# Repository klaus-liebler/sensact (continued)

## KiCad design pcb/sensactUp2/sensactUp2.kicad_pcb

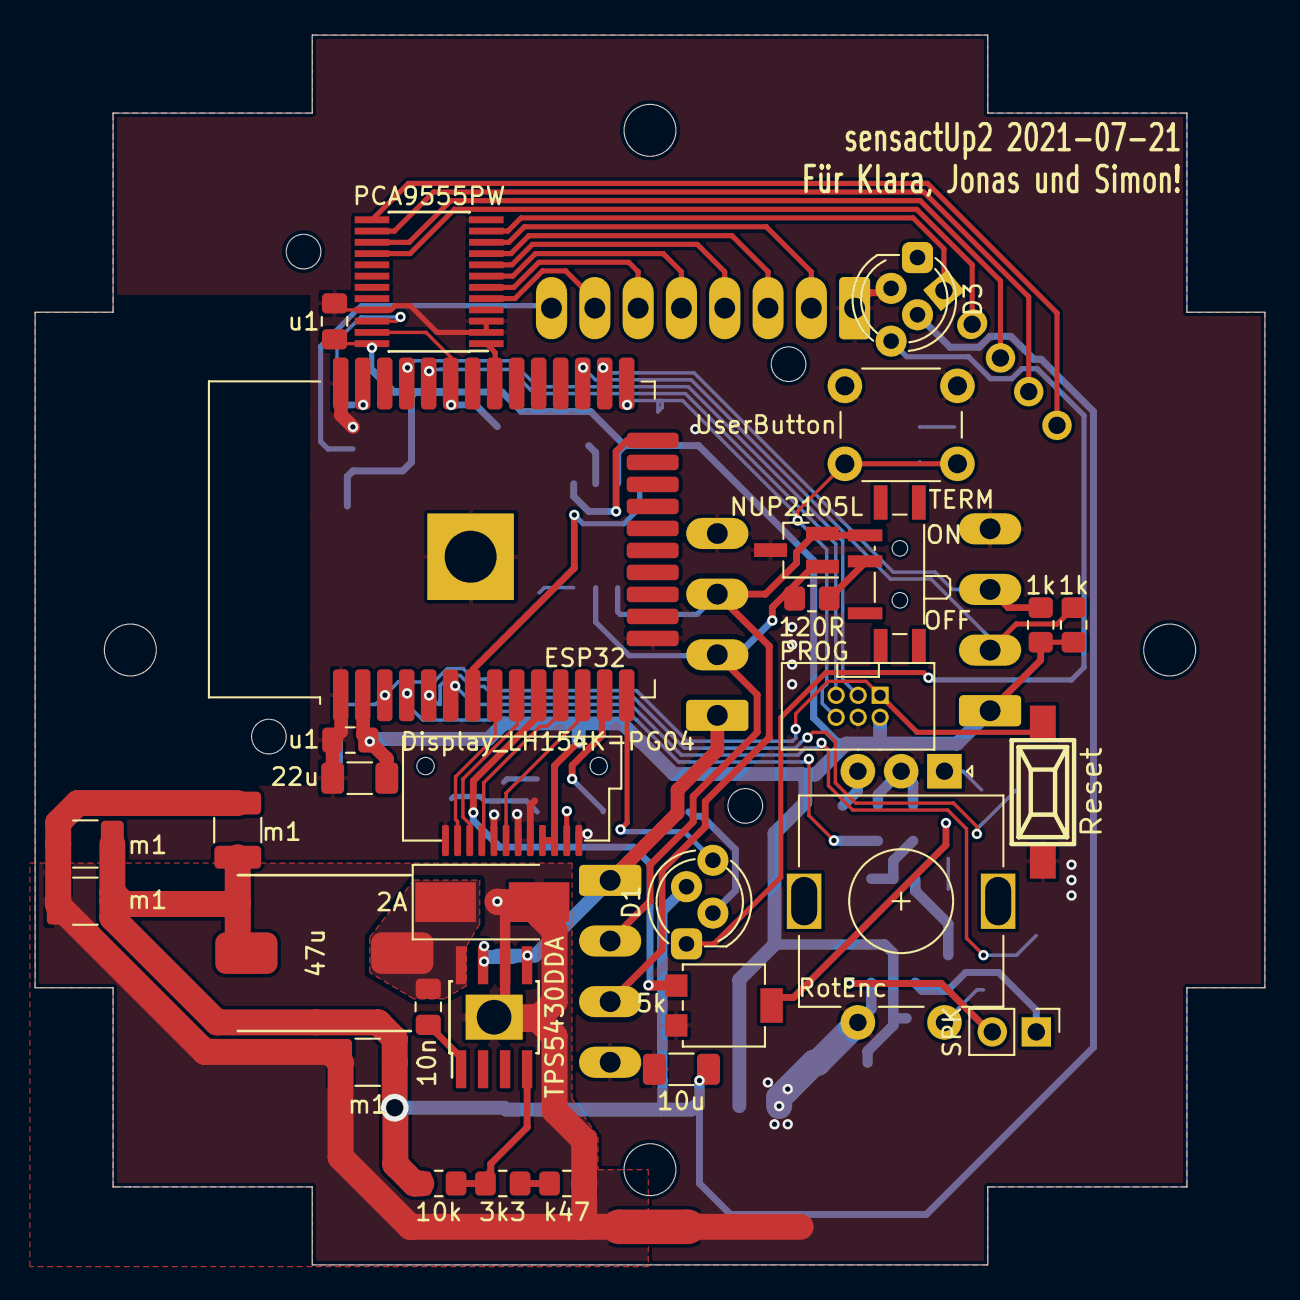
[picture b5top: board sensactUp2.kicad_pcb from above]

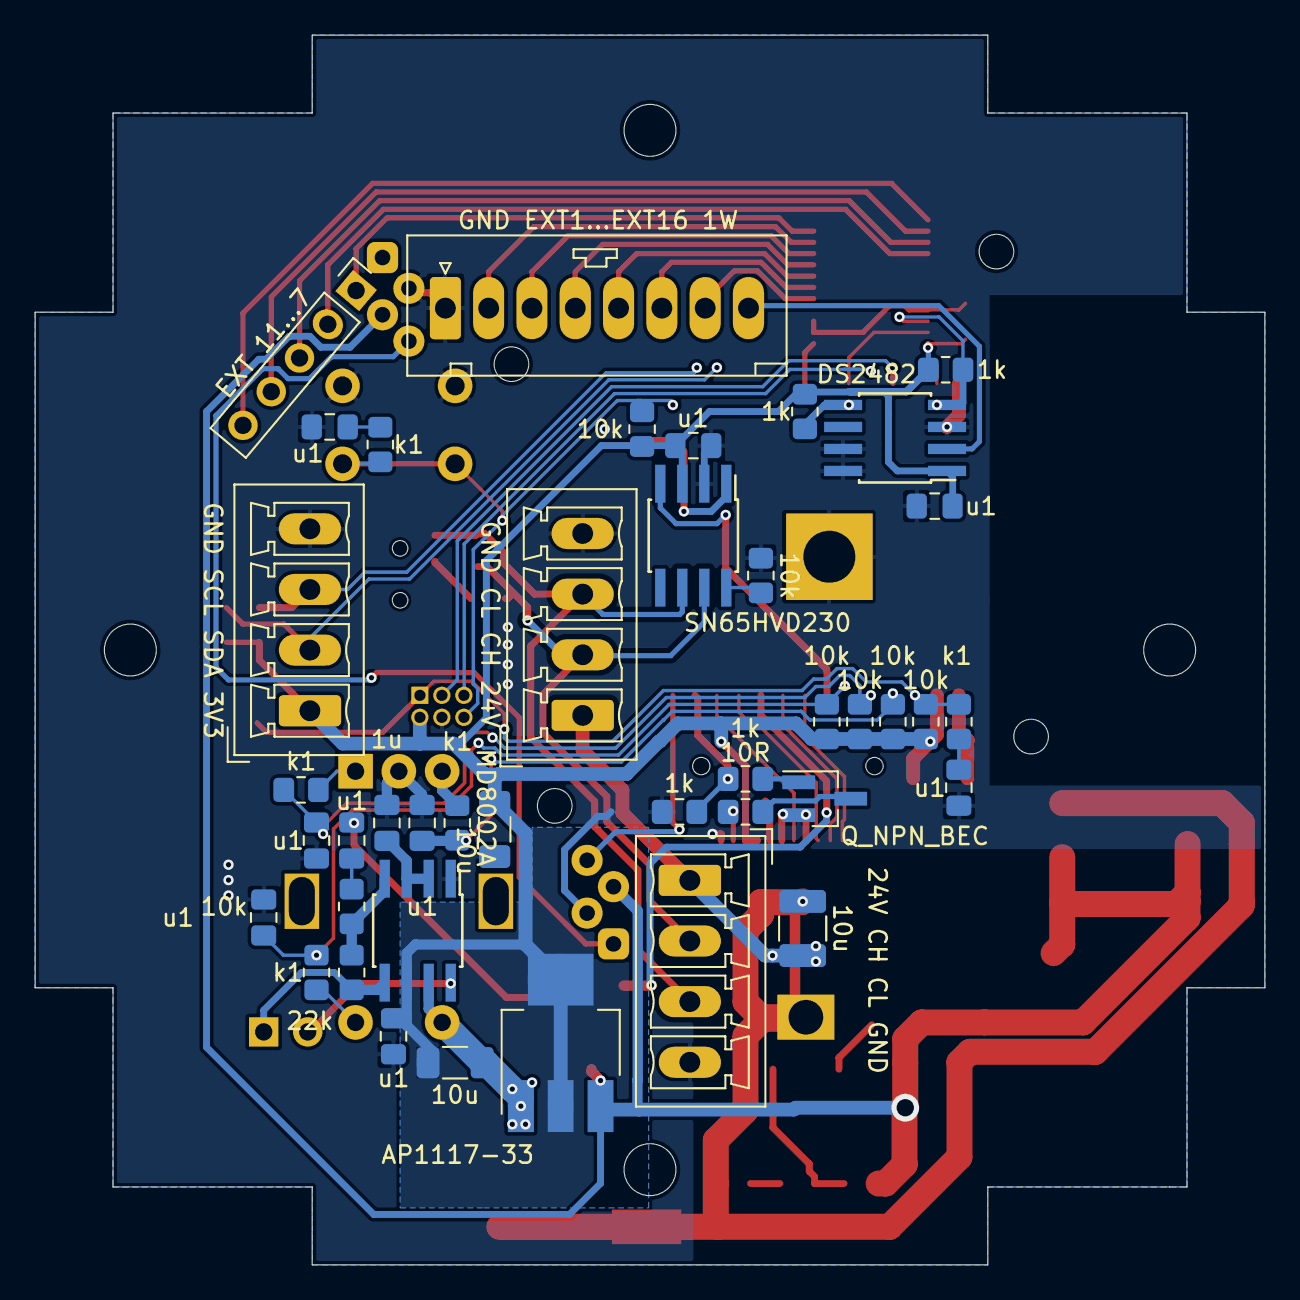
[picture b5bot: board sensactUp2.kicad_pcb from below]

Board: 2 copper layers, 71.0 x 71.0 mm, 73 parts (41 on the bottom side), 61 nets.

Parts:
C1: 22u; C_1206_3216Metric_Pad1.33x1.80mm_HandSolder
C2, C3, C4, C5, C7, C8, C9, C10, C18, C21, C22: u1; C_0805_2012Metric_Pad1.18x1.45mm_HandSolder
C6: 1u; C_0805_2012Metric_Pad1.18x1.45mm_HandSolder
C11, C19, C20: 10u; C_1206_3216Metric_Pad1.33x1.80mm_HandSolder
C12: 10u; C_1210_3225Metric_Pad1.33x2.70mm_HandSolder
C13: 10n; C_0805_2012Metric_Pad1.18x1.45mm_HandSolder
C14, C15, C16, C17: m1; C_1210_3225Metric_Pad1.33x2.70mm_HandSolder
D1: ROT_LED; LED_D5.0mm-4_RGB_Staggered_Pins
D2: 2A; D_SMB_Handsoldering
D3: USER_LED; LED_D5.0mm-4_RGB_Staggered_Pins
D4: NUP2105L; SOT-23_Handsoldering
IC1: MD8002A; SOIC-8_3.9x4.9mm_Pitch1.27mm_handsolder
J1: PROG; IDC_2x03_P1.27mm_Vertical
J2: GND CL CH 24V; PhoenixContact_MCV_1,5_4-G-3.5_1x04_P3.50mm_Vertical
J3: GND SCL SDA 3V3; PhoenixContact_MCV_1,5_4-G-3.5_1x04_P3.50mm_Vertical
J4: GND EXT1...EXT16 1W; PhoenixContact_MCV_0,5_8-G-2.5_1x08_P2.50mm_vertical
J5: 24V CH CL GND; PhoenixContact_MCV_1,5_4-G-3.5_1x04_P3.50mm_Vertical
J6: EXT 11...7; PinHeader_1x05_P2.54mm_Vertical
J7: SPK; PinHeader_1x02_P2.54mm_Vertical
L1: 47u; Inductor_CDRH104_handsolder
NT1: Net-Tie_2; NetTie-2_SMD_Pad2.0mm
Q3: Q_NPN_BEC; SOT-23_Handsoldering
R1, R2, R6, R7, R9, R10, R15, R18: 10k; R_0805_2012Metric_Pad1.20x1.40mm_HandSolder
R3, R4, R5, R14, R16: k1; R_0805_2012Metric_Pad1.20x1.40mm_HandSolder
R8: 22k; R_0805_2012Metric_Pad1.20x1.40mm_HandSolder
R11: 3k3; R_0805_2012Metric_Pad1.20x1.40mm_HandSolder
R12: k47; R_0805_2012Metric_Pad1.20x1.40mm_HandSolder
R13, R20, R21, R22, R23, R52: 1k; R_0805_2012Metric_Pad1.20x1.40mm_HandSolder
R17: 10R; R_0805_2012Metric_Pad1.20x1.40mm_HandSolder
R19: 120R; R_0805_2012Metric_Pad1.20x1.40mm_HandSolder
RV1: 5k; Potentiometer_Bourns_3314G_Vertical
SW1: RotEnc; RotaryEncoder_Alps_EC11E-Switch_Vertical_H20mm
SW2: Reset; smd_push_handsolder
SW3: UserButton; SW_PUSH_6mm_H13mm
SW4: TERM; SW_SPDT_PCM12_handsolder
U1: ESP32; ESP32-WROOM-32_HANDSOLDER
U2: TPS5430DDA; SOIC-8_3.9x4.9mm_Pitch1.27mm_pad_handsolder
U3: DS2482; SOIC-8_3.9x4.9mm_Pitch1.27mm_handsolder
U4: SN65HVD230; SOIC-8_3.9x4.9mm_Pitch1.27mm_handsolder
U5: AP1117-33; SOT-223-3_TabPin2_HANDSOLDER
U6: PCA9555PW; TSSOP-24_4.4x7.8mm_Pitch0.65mm_handsolder
X1: Display_LH154K-PG04

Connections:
1W: J4.8, U3.2
+3V3: C1.1, C2.1, C8.1, C9.1, C10.1, C11.1, C20.1, C22.1, IC1.6, J1.2, J3.1, R1.2, R2.2, R6.1, R15.1, R18.1, R20.1, R21.1, R22.1, R23.1, U1.2, U3.1, U4.3, U5.2, U6.24, X1.3, X1.4
+4V: C14.1, C15.1, C16.1, C17.1, C19.1, D1.3, D3.3, L1.1, R10.1, U5.3
+24V: C12.1, J2.1, J5.1, U2.5, U2.7
/LEDK: R17.1, X1.2
/psu/SW: C13.1, D2.1, L1.2, U2.8
/psu/VSENSE: R10.2, R11.1, U2.4
CANH: D4.1, J2.2, J5.2, R19.1, U4.7
CANL: D4.2, J2.3, J5.3, SW4.3, U4.6
CANR: U1.7, U4.4
CANT: U1.24, U4.1
EN: J1.1, R14.1, R15.2, SW2.2, U1.3
EXT1: J4.2, U6.10
EXT2: J4.3, U6.9
EXT3: J4.4, U6.8
EXT4: J4.5, U6.7
EXT5: J4.6, U6.6
EXT6: J4.7, U6.5
EXT7: J6.1, U6.11
EXT8: J6.2, U6.16
EXT9: J6.3, U6.15
EXT10: J6.4, U6.14
EXT11: J6.5, U6.13
EXT_SCL: J3.3, R23.2, U1.26
EXT_SDA: J3.2, R22.2, U1.27
GND: C12.2, C14.2, C15.2, C16.2, C17.2, D2.2, NT1.1, R12.2, U2.6, U2.9
GNDD: C1.2, C2.2, C3.1, C4.1, C5.1, C6.2, C8.2, C9.2, C10.2, C11.2, C18.2, C19.2, C20.2, C21.2, C22.2, D1.2, D3.2, D4.3, IC1.1, IC1.7, J1.4, J2.4, J3.4, J4.1, J5.4, NT1.2, Q3.2, R9.2, R52.2, RV1.3, SW1.C, SW1.S1, SW2.1, SW3.2, U1.1, U1.15, U1.38, U1.39, U3.3, U3.7, U3.8, U4.2, U5.1, U6.2, U6.3, U6.12, U6.21, X1.1, X1.5, X1.6, X1.8, X1.12
I2C_SCL: R21.2, U1.37, U3.4, U6.22
I2C_SDA: R20.2, U1.33, U3.5, U6.23
IO0: J1.6, R16.1, R18.2, SW3.1, U1.25
LCD_BL: R13.2, R52.1, U1.13
LCD_CLK: U1.11, X1.9
LCD_DC: U1.12, X1.7
LCD_MOSI: U1.9, X1.10
LCD_RES: U1.8, X1.11
LED: D1.4, U1.14
unnamed: C6.1, IC1.2, IC1.3
unnamed: C7.1, R7.2
unnamed: C7.2, RV1.2
unnamed: C13.2, U2.1
unnamed: C18.1, R14.2
unnamed: C21.1, R16.2
unnamed: D1.1, D3.4
unnamed: IC1.4, R7.1, R8.2
unnamed: IC1.5, J7.1, R8.1
unnamed: IC1.8, J7.2
unnamed: Q3.1, R13.1
unnamed: Q3.3, R17.2
unnamed: R3.1, SW1.A
unnamed: R4.1, SW1.B
unnamed: R5.2, SW1.S2
unnamed: R9.1, U4.8
unnamed: R11.2, R12.1
unnamed: R19.2, SW4.2
PCA_INT: U1.31, U6.1
ROT1_A: C3.2, R1.1, R3.2, U1.5
ROT1_B: C4.2, R2.1, R4.2, U1.4
ROT1_S: C5.2, R5.1, R6.2, U1.6
RXD0: J1.5, U1.34
SPK_OUT: RV1.1, U1.10
TXD0: J1.3, U1.35

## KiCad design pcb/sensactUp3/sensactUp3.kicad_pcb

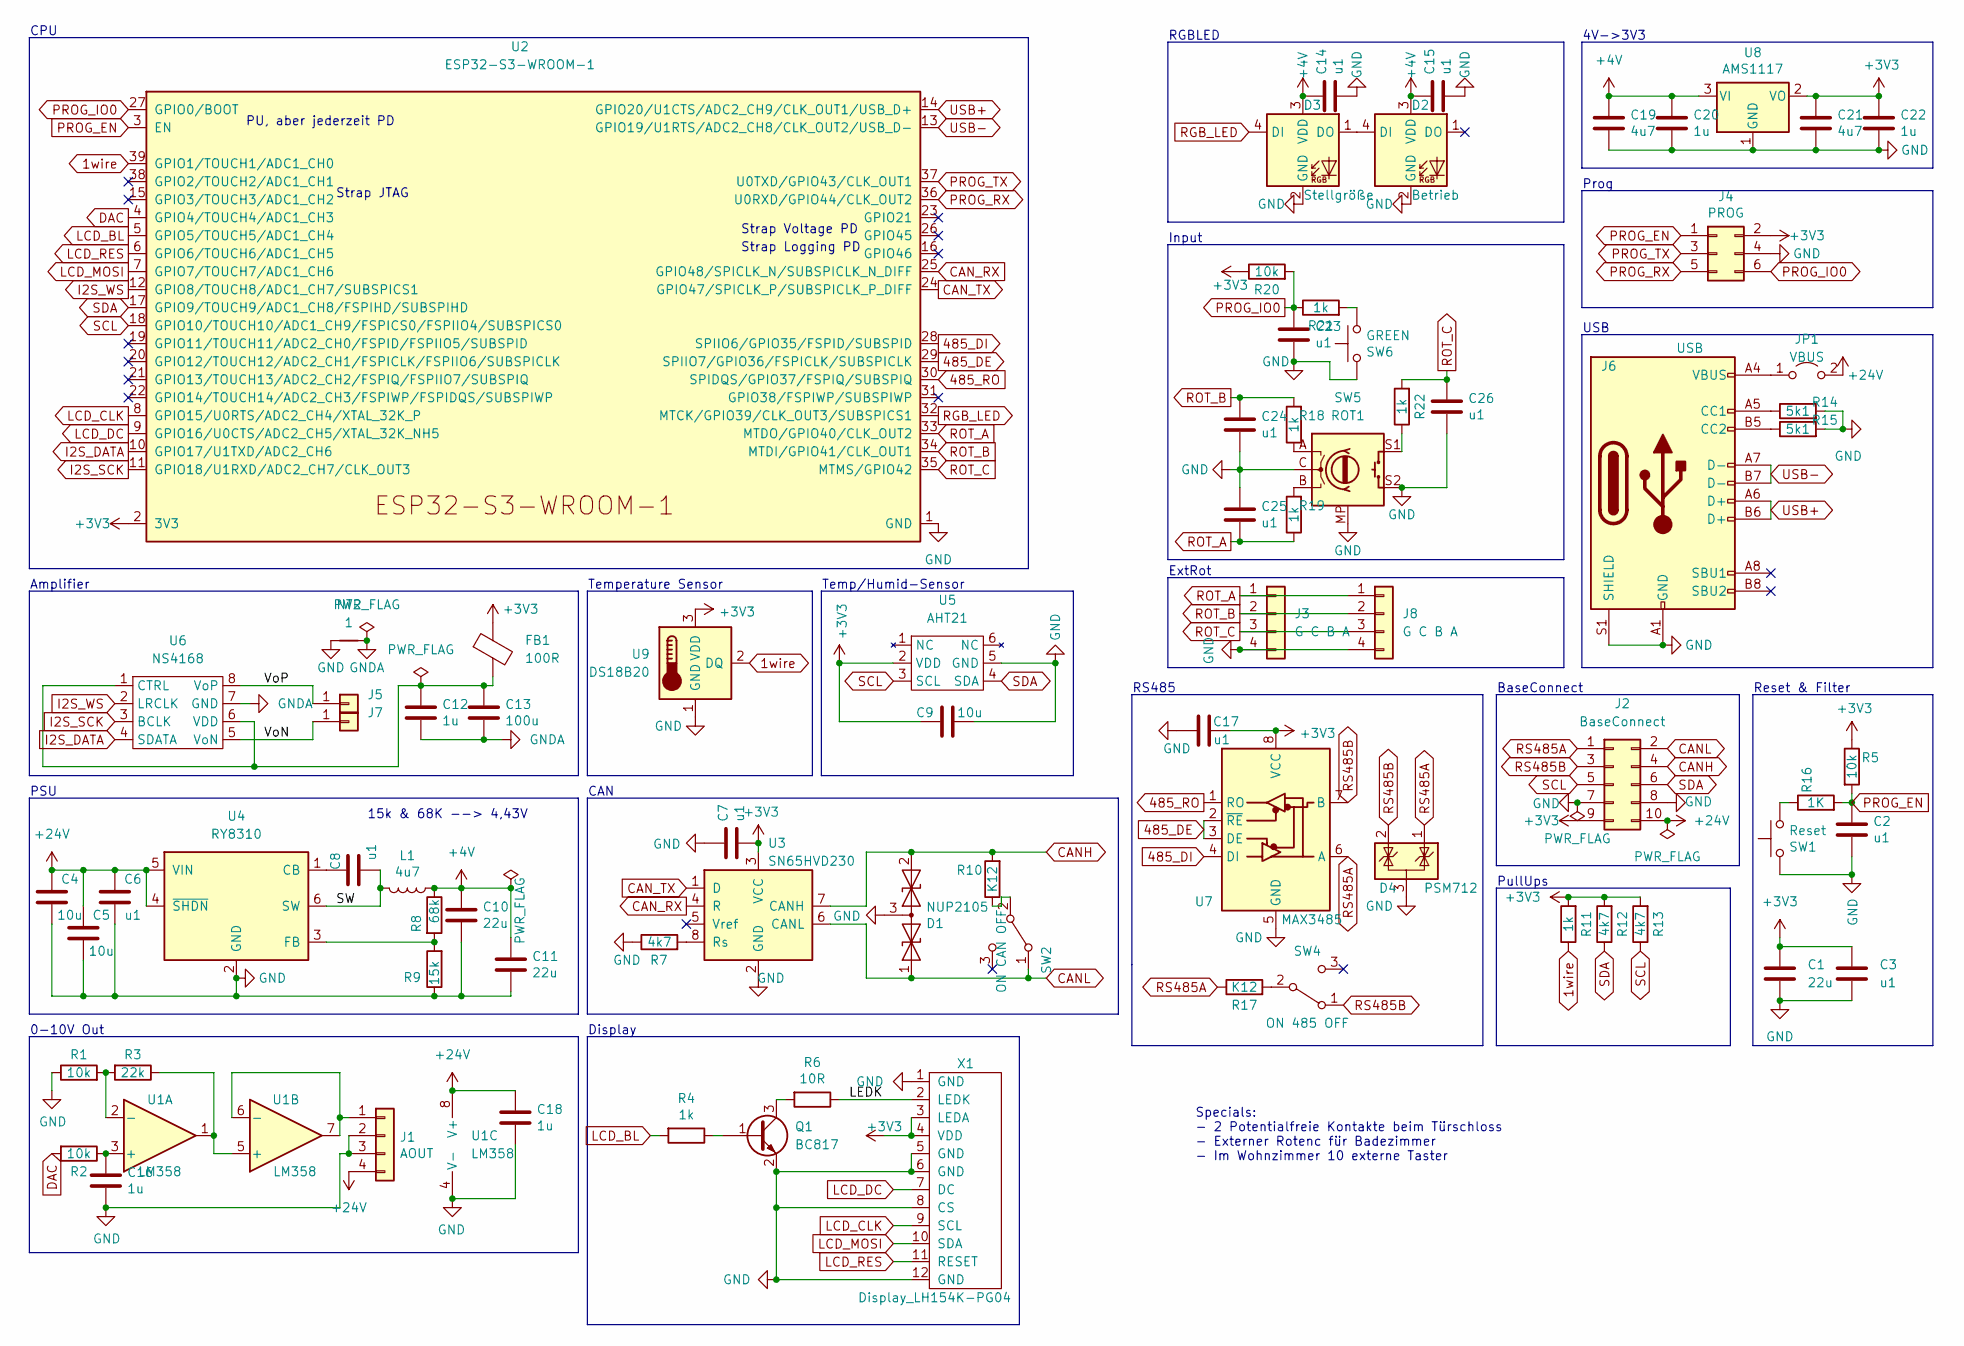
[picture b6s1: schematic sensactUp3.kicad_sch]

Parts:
C1, C10, C11: 22u; C_0603_1608Metric
C2, C3, C6, C7, C8, C14, C15, C17, C23, C24, C25, C26: u1; C_0402_1005Metric
C4, C5, C9: 10u; C_0805_2012Metric
C12, C16, C18, C20, C22: 1u; C_0402_1005Metric
C13: 100u; C_1206_3216Metric
C19, C21: 4u7; C_0402_1005Metric
D1: NUP2105; SOT-23_Handsoldering
D2: Betrieb; LED_D5.0mm-4_RGB_Staggered_Pins
D3: Stellgröße; LED_D5.0mm-4_RGB_Staggered_Pins
D4: PSM712; SOT-23_Handsoldering
FB1: 100R; L_0805_2012Metric
J1: AOUT; JST_XH_S4B-XH-A_1x04_P2.50mm_Horizontal
J2: BaseConnect; IDC-Header_2x05_P2.54mm_Vertical
J3: G C B A; PinHeader_1x04_P2.54mm_Vertical
J4: PROG; IDC_2x03_P1.27mm_Vertical
J5: S+; TestPoint_THTPad_1.5x1.5mm_Drill0.7mm
J6: USB; GT-USB-7051A
J7: S-; TestPoint_THTPad_1.5x1.5mm_Drill0.7mm
J8: G C B A; PhoenixContact_MCV_1,5_4-G-3.5_1x04_P3.50mm_Vertical
JP1: VBUS; SolderJumper-2_P1.3mm_Open_RoundedPad1.0x1.5mm
L1: 4u7; L_Abracon_ASPI-0630LR
NT2: 1; NetTie-2_SMD_Pad0.5mm
Q1: BC817; SOT-23_smaller
R1, R2, R5, R20: 10k; R_0402_1005Metric
R3: 22k; R_0402_1005Metric
R4, R18, R19, R21, R22: 1k; R_0402_1005Metric
R6: 10R; R_0805_2012Metric
R7, R12, R13: 4k7; R_0402_1005Metric
R8: 68k; R_0402_1005Metric
R9: 15k; R_0402_1005Metric
R10, R17: K12; R_1206_3216Metric_Pad1.30x1.75mm_HandSolder
R11: 1k; R_0603_1608Metric
R14, R15: 5k1; R_0402_1005Metric
R16: 1K; R_0402_1005Metric
SW1: Reset; SW_SPST_TL3342
SW2: ON CAN OFF; Switch_SS12D00
SW4: ON 485 OFF; Switch_SS12D00
SW5: ROT1; RotaryEncoder_Alps_EC11E-Switch_Vertical_H20mm
SW6: GREEN; SW_PUSH_6mm_H13mm
U1: LM358; SOIC-8_3.9x4.9mm_P1.27mm
U2: ESP32-S3-WROOM-1
U3: SN65HVD230; SOIC-8_3.9x4.9mm_P1.27mm
U4: RY8310; SOT-23-6
U5: AHT21
U6: NS4168; SOIC-8_3.9x4.9mm_Pitch1.27mm_pad_handsolder
U7: MAX3485; SOIC-8_3.9x4.9mm_P1.27mm
U8: AMS1117; SOT-223-3_TabPin2
U9: DS18B20; TO-92_HandSolder
X1: Display_LH154K-PG04; Display_LH154K-PG04_variant

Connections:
1wire: R11.1, U2.39 (GPIO1/TOUCH1/ADC1_CH0), U9.2 (DQ)
485_DE: U2.29 (SPIIO7/GPIO36/FSPICLK/SUBSPICLK), U7.2 (~RE), U7.3 (DE)
485_DI: U2.28 (SPIIO6/GPIO35/FSPID/SUBSPID), U7.4 (DI)
485_RO: U2.30 (SPIDQS/GPIO37/FSPIQ/SUBSPIQ), U7.1 (RO)
+3V3: C1.1, C3.1, C7.2, C9.1, C17.1, C21.2, C22.1, FB1.1, J2.9, J4.2, R5.1, R11.2, R12.2, R13.2, R20.1, U2.2 (3V3), U3.3 (VCC), U5.2 (VDD), U7.8 (VCC), U8.2 (VO), U9.3 (VDD), X1.3 (LEDA), X1.4 (VDD)
+4V: C10.1, C11.1, C14.1, C15.1, C19.2, C20.1, D2.3 (VDD), D3.3 (VDD), L1.1, R8.1, U8.3 (VI)
+24V: C4.2, C5.2, C6.2, C18.1, J1.4, J2.10, JP1.2 (B), U1.8 (V+), U4.4 (~SHDN), U4.5 (VIN)
/LEDK: R6.1, X1.2 (LEDK)
/SW: C8.1, L1.2, U4.6 (SW)
/VoN: J7.1, U6.5 (VoN)
/VoP: J5.1, U6.8 (VoP)
CANH: D1.2 (A2), J2.4, R10.2, U3.7 (CANH)
CANL: D1.1 (A1), J2.2, SW2.1 (A), U3.6 (CANL)
CAN_RX: U2.25 (GPIO48/SPICLK_N/SUBSPICLK_N_DIFF), U3.4 (R)
CAN_TX: U2.24 (GPIO47/SPICLK_P/SUBSPICLK_P_DIFF), U3.1 (D)
DAC: R2.2, U2.4 (GPIO4/TOUCH4/ADC1_CH3)
GND: C1.2, C2.2, C3.2, C4.1, C5.1, C6.1, C7.1, C9.2, C10.2, C11.2, C14.2, C15.2, C16.2, C17.2, C18.2, C19.1, C20.2, C21.1, C22.2, C23.1, C24.1, C25.2, C26.1, D1.3 (common), D2.2 (GND), D3.2 (GND), D4.3 (A), J1.2, J1.3, J2.7, J2.8, J3.4, J4.4, J6.A1 (GND), J6.A12 (GND), J6.B1 (GND), J6.B12 (GND), J6.S1 (SHIELD), J8.4, NT2.1, Q1.2 (E), R1.1, R7.1, R9.1, R14.2, R15.2, SW1.2, SW5.C, SW5.MP, SW5.S2, SW6.2, U1.4 (V-), U2.1 (GND), U2.40 (GND), U2.41 (GND), U3.2 (GND), U4.2 (GND), U5.5 (GND), U7.5 (GND), U8.1 (GND), U9.1 (GND), X1.1 (GND), X1.5 (GND), X1.6 (GND), X1.8 (CS), X1.12 (GND)
GNDA: C12.2, C13.2, NT2.2, U6.7 (GND)
I2S_DATA: U2.10 (GPIO17/U1TXD/ADC2_CH6), U6.4 (SDATA)
I2S_SCK: U2.11 (GPIO18/U1RXD/ADC2_CH7/CLK_OUT3), U6.3 (BCLK)
I2S_WS: U2.12 (GPIO8/TOUCH8/ADC1_CH7/SUBSPICS1), U6.2 (LRCLK)
LCD_BL: R4.2, U2.5 (GPIO5/TOUCH5/ADC1_CH4)
LCD_CLK: U2.8 (GPIO15/U0RTS/ADC2_CH4/XTAL_32K_P), X1.9 (SCL)
LCD_DC: U2.9 (GPIO16/U0CTS/ADC2_CH5/XTAL_32K_NH5), X1.7 (DC)
LCD_MOSI: U2.7 (GPIO7/TOUCH7/ADC1_CH6), X1.10 (SDA)
LCD_RES: U2.6 (GPIO6/TOUCH6/ADC1_CH5), X1.11 (RESET)
unnamed: D2.4 (DI), D3.1 (DO)
unnamed: J1.1, U1.6 (-), U1.7
unnamed: J6.A5 (CC1), R14.1
unnamed: J6.B5 (CC2), R15.1
unnamed: J6.A4 (VBUS), J6.A9 (VBUS), J6.B4 (VBUS), J6.B9 (VBUS), JP1.1 (A)
unnamed: Q1.1 (B), R4.1
unnamed: Q1.3 (C), R6.2
unnamed: R16.1, SW1.1
unnamed: R18.1, SW5.A
unnamed: R19.2, SW5.B
unnamed: R21.2, SW6.1
unnamed: R22.1, SW5.S1
unnamed: R10.1, SW2.2 (B)
unnamed: R17.2, SW4.2 (B)
unnamed: C16.1, R2.1, U1.3 (+)
unnamed: R1.2, R3.2, U1.2 (-)
unnamed: R3.1, U1.1, U1.5 (+)
unnamed: R7.2, U3.8 (Rs)
unnamed: C8.2, U4.1 (CB)
unnamed: R8.2, R9.2, U4.3 (FB)
unnamed: C12.1, C13.1, FB1.2, U6.1 (CTRL), U6.6 (VDD)
PROG_EN: C2.1, J4.1, R5.2, R16.2, U2.3 (EN)
PROG_IO0: C23.2, J4.6, R20.2, R21.1, U2.27 (GPIO0/BOOT)
PROG_RX: J4.5, U2.36 (U0RXD/GPIO44/CLK_OUT2)
PROG_TX: J4.3, U2.37 (U0TXD/GPIO43/CLK_OUT1)
RGB_LED: D3.4 (DI), U2.32 (MTCK/GPIO39/CLK_OUT3/SUBSPICS1)
ROT_A: C25.1, J3.1, J8.1, R19.1, U2.33 (MTDO/GPIO40/CLK_OUT2)
ROT_B: C24.2, J3.2, J8.2, R18.2, U2.34 (MTDI/GPIO41/CLK_OUT1)
ROT_C: C26.2, J3.3, J8.3, R22.2, U2.35 (MTMS/GPIO42)
RS485A: D4.1 (K), J2.1, R17.1, U7.6 (A)
RS485B: D4.2 (K), J2.3, SW4.1 (A), U7.7 (B)
SCL: J2.5, R13.1, U2.18 (GPIO10/TOUCH10/ADC1_CH9/FSPICS0/FSPIIO4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), U5.3 (SCL)
SDA: J2.6, R12.1, U2.17 (GPIO9/TOUCH9/ADC1_CH8/FSPIHD/SUBSPIHD), U5.4 (SDA)
USB+: J6.A6 (D+), J6.B6 (D+), U2.14 (GPIO20/U1CTS/ADC2_CH9/CLK_OUT1/USB_D+)
USB-: J6.A7 (D-), J6.B7 (D-), U2.13 (GPIO19/U1RTS/ADC2_CH8/CLK_OUT2/USB_D-)

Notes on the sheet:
Prog
0-10V Out
PullUps
15k & 68K --> 4,43V
Input
PU, aber jederzeit PD
Temp/Humid-Sensor
RGBLED
Strap Voltage PD
4V->3V3
PSU
CPU
Display
Strap Logging PD
ExtRot
Amplifier
BaseConnect
Temperature Sensor
Strap JTAG
Specials: - 2 Potentialfreie Kontakte beim Türschloss - Externer Rotenc für Badezimmer - Im Wohnzimmer 10 externe Taster
USB
CAN
RS485
Reset & Filter

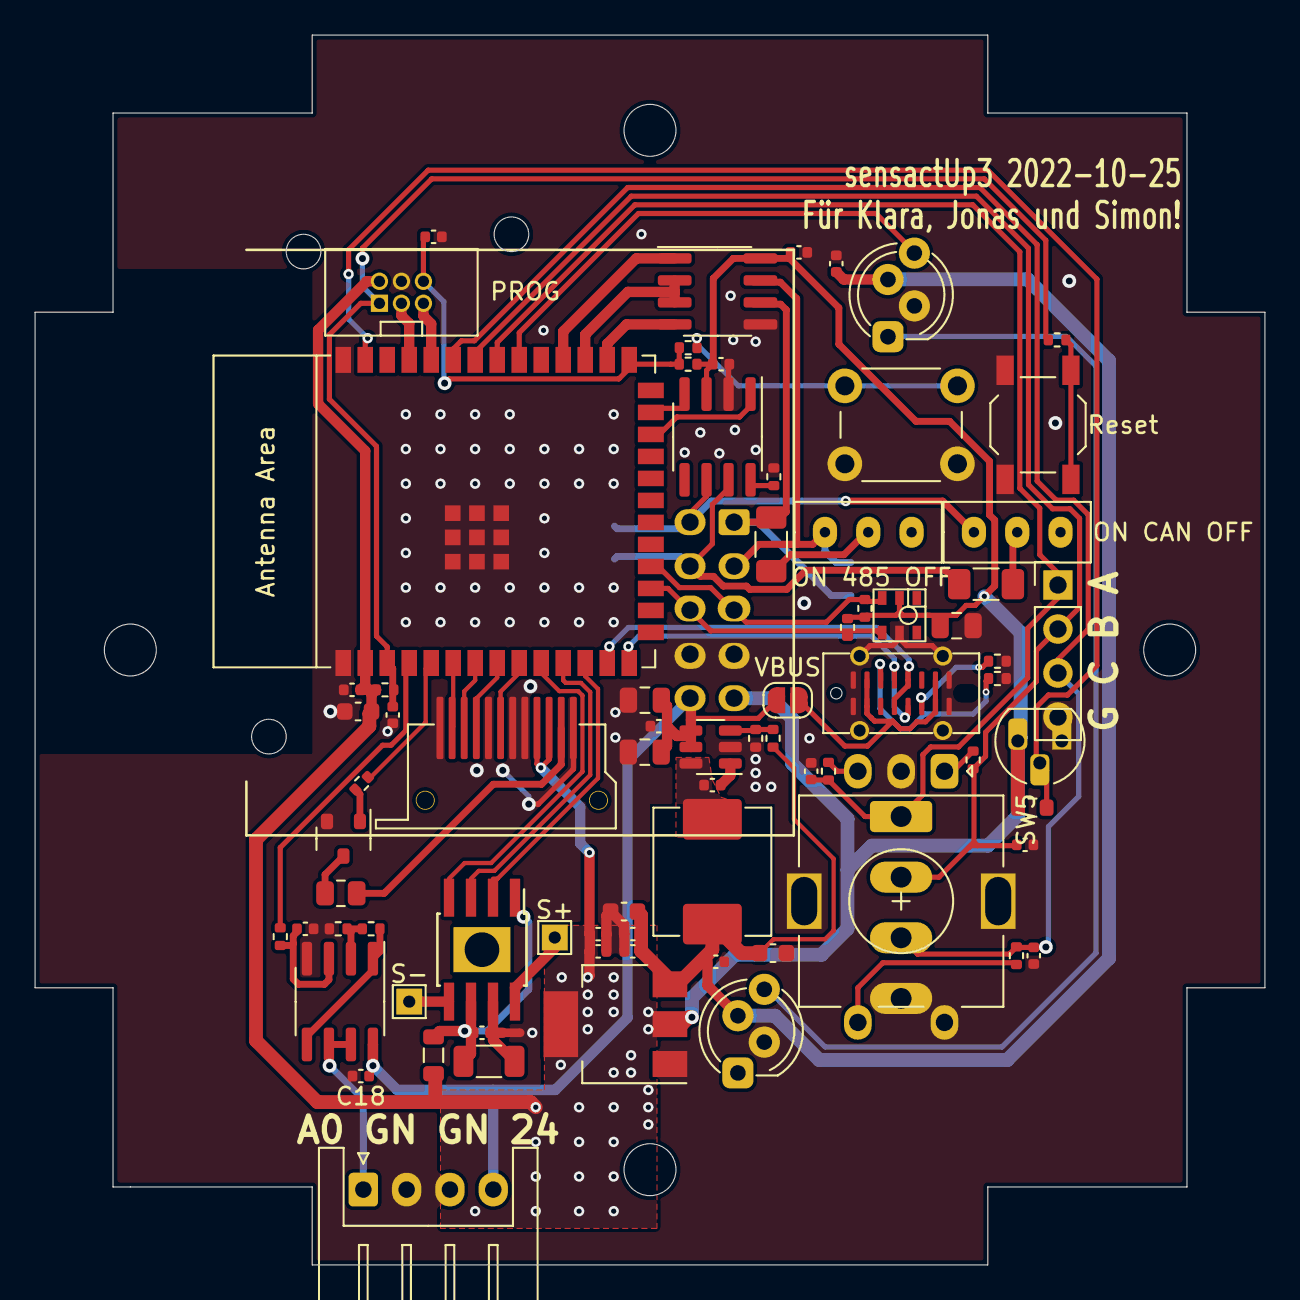
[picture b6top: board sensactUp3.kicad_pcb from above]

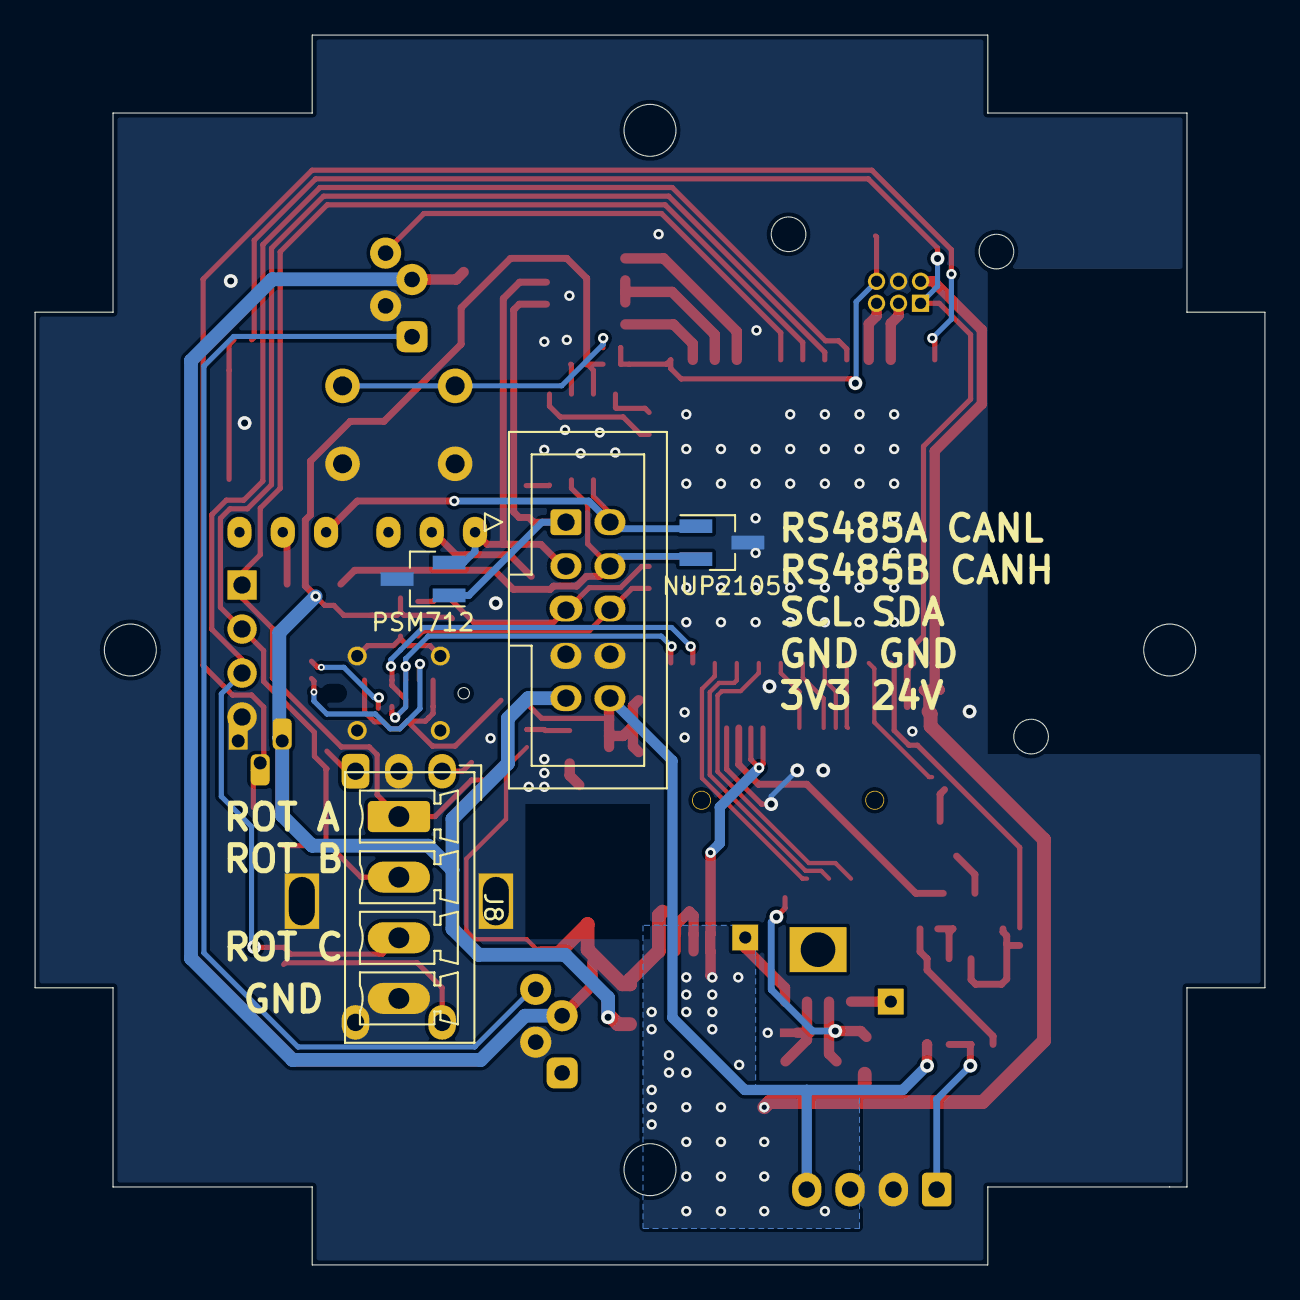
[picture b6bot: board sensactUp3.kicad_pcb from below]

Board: 2 copper layers, 71.0 x 71.0 mm, 80 parts (4 on the bottom side), 61 nets.

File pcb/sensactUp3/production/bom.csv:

Designator,Footprint,Quantity,Value,LCSC Part #
C1,0603,1,22u,
C10,0603,1,22u,
C11,0603,1,22u,
C12,0402,1,1u,
C13,1206,1,100u,
C14,0402,1,u1,
C15,0402,1,u1,
C16,0402,1,1u,
C17,0402,1,u1,
C18,0402,1,1u,
C19,0402,1,4u7,
C2,0402,1,u1,
C20,0402,1,1u,
C21,0402,1,4u7,
C22,0402,1,1u,
C23,0402,1,u1,
C24,0402,1,u1,
C25,0402,1,u1,
C26,0402,1,u1,
C3,0402,1,u1,
C4,0805,1,10u,
C5,0805,1,10u,
C6,0402,1,u1,
C7,0402,1,u1,
C8,0402,1,u1,
C9,0805,1,10u,
D1,SOT-23_Handsoldering,1,NUP2105,
D2,LED_D5.0mm-4_RGB_Staggered_Pins,1,Betrieb,
D3,LED_D5.0mm-4_RGB_Staggered_Pins,1,Stellgröße,
D4,SOT-23_Handsoldering,1,PSM712,
FB1,0805,1,100R,
J1,JST_XH_S4B-XH-A_1x04_P2.50mm_Horizontal,1,AOUT,
J2,IDC-Header_2x05_P2.54mm_Vertical,1,BaseConnect,
J3,PinHeader_1x04_P2.54mm_Vertical,1,G C B A,
J4,IDC_2x03_P1.27mm_Vertical,1,PROG,
J5,TestPoint_THTPad_1.5x1.5mm_Drill0.7mm,1,S+,
J6,GT-USB-7051A,1,USB,
J7,TestPoint_THTPad_1.5x1.5mm_Drill0.7mm,1,S-,
J8,"PhoenixContact_MCV_1,5_4-G-3.5_1x04_P3.50mm_Vertical",1,G C B A,
L1,L_Abracon_ASPI-0630LR,1,4u7,
NT2,NetTie-2_SMD_Pad0.5mm,1,1,
Q1,SOT-23_smaller,1,BC817,
R1,0402,1,10k,
R10,1206,1,K12,
R11,0603,1,1k,
R12,0402,1,4k7,
R13,0402,1,4k7,
R14,0402,1,5k1,
R15,0402,1,5k1,
R16,0402,1,1K,
R17,1206,1,K12,
R18,0402,1,1k,
R19,0402,1,1k,
R2,0402,1,10k,
R20,0402,1,10k,
R21,0402,1,1k,
R22,0402,1,1k,
R3,0402,1,22k,
R4,0402,1,1k,
R5,0402,1,10k,
R6,0805,1,10R,
R7,0402,1,4k7,
R8,0402,1,68k,
R9,0402,1,15k,
SW1,SW_SPST_TL3342,1,Reset,
SW2,Switch_SS12D00,1,ON CAN OFF,
SW4,Switch_SS12D00,1,ON 485 OFF,
SW5,RotaryEncoder_Alps_EC11E-Switch_Vertical_H20mm,1,ROT1,
SW6,SW_PUSH_6mm_H13mm,1,GREEN,
U1,SOIC-8_3.9x4.9mm_P1.27mm,1,LM358,
U2,ESP32-S3-WROOM-1,1,ESP32-S3-WROOM-1,
U3,SOIC-8_3.9x4.9mm_P1.27mm,1,SN65HVD230,
U4,SOT-23-6,1,RY8310,
U5,AHT21,1,AHT21,
U6,SOIC-8_3.9x4.9mm_Pitch1.27mm_pad_handsolder,1,NS4168,
U7,SOIC-8_3.9x4.9mm_P1.27mm,1,MAX3485,
U8,SOT-223-3_TabPin2,1,AMS1117,
U9,TO-92_HandSolder,1,DS18B20,
X1,Display_LH154K-PG04_variant,1,Display_LH154K-PG04,

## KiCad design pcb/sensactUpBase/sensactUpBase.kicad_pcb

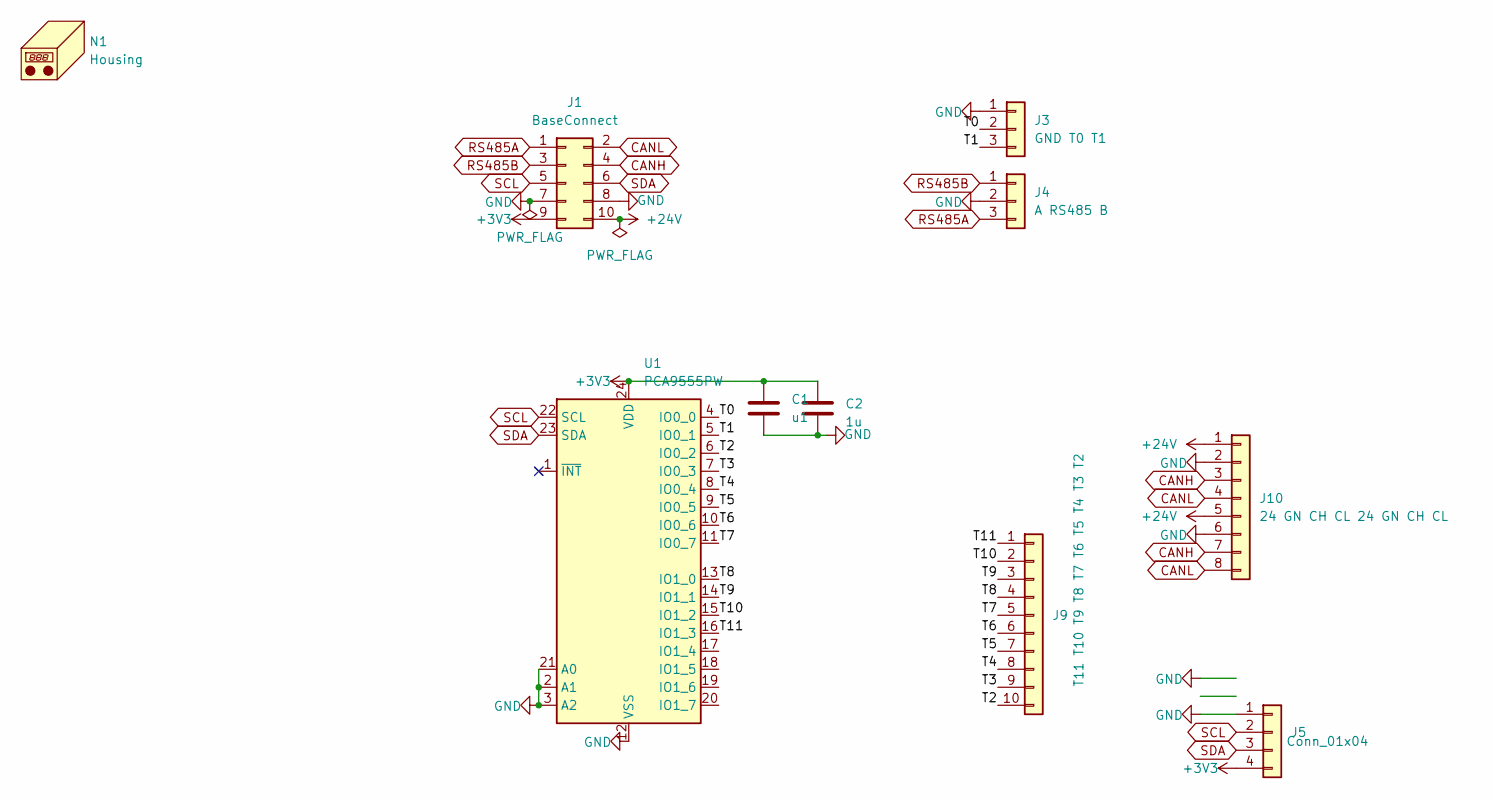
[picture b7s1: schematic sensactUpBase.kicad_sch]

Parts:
C1: u1; C_0805_2012Metric_Pad1.18x1.45mm_HandSolder
C2: 1u; C_0805_2012Metric_Pad1.18x1.45mm_HandSolder
J1: BaseConnect; IDC-Header_2x05_P2.54mm_Vertical
J3: GND T0 T1; KF250-3.5-3P-A
J4: A RS485 B; KF250-3.5-3P-A
J5: Conn_01x04; PinHeader_1x04_P2.54mm_Vertical
J9: T11 T10 T9 T8 T7 T6 T5 T4 T3 T2; WAGO_250-210
J10: 24 GN CH CL 24 GN CH CL; WAGO_250-208
N1: Housing; KiCad-Logo2_5mm_SilkScreen
U1: PCA9555PW; TSSOP-24_4.4x7.8mm_Pitch0.65mm_handsolder

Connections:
+3V3: C1.1, C2.1, J1.9, J5.4, U1.24 (VDD)
+24V: J1.10, J10.1, J10.5
/T0: J3.2, U1.4 (IO0_0)
/T1: J3.3, U1.5 (IO0_1)
/T2: J9.10, U1.6 (IO0_2)
/T3: J9.9, U1.7 (IO0_3)
/T4: J9.8, U1.8 (IO0_4)
/T5: J9.7, U1.9 (IO0_5)
/T6: J9.6, U1.10 (IO0_6)
/T7: J9.5, U1.11 (IO0_7)
/T8: J9.4, U1.13 (IO1_0)
/T9: J9.3, U1.14 (IO1_1)
/T10: J9.2, U1.15 (IO1_2)
/T11: J9.1, U1.16 (IO1_3)
CANH: J1.4, J10.3, J10.7
CANL: J1.2, J10.4, J10.8
GND: C1.2, C2.2, J1.7, J1.8, J3.1, J4.2, J5.1, J10.2, J10.6, U1.2 (A1), U1.3 (A2), U1.12 (VSS), U1.21 (A0)
RS485A: J1.1, J4.3
RS485B: J1.3, J4.1
SCL: J1.5, J5.2, U1.22 (SCL)
SDA: J1.6, J5.3, U1.23 (SDA)

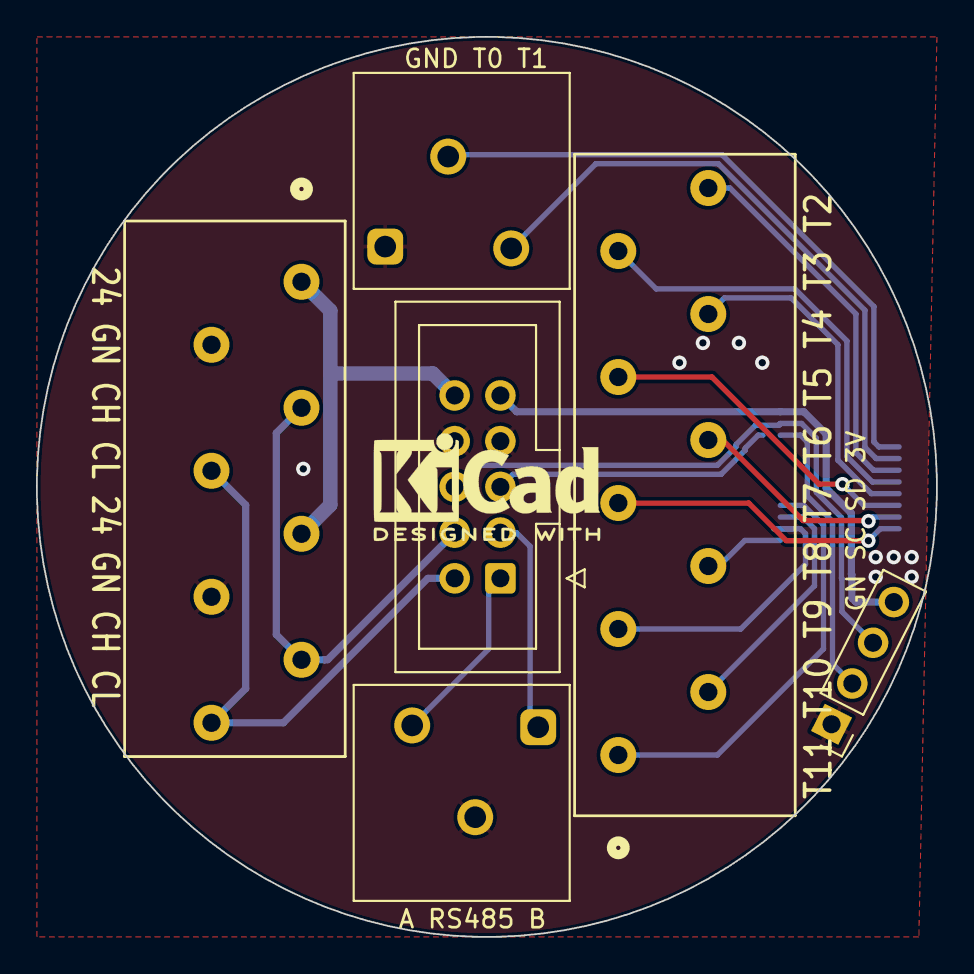
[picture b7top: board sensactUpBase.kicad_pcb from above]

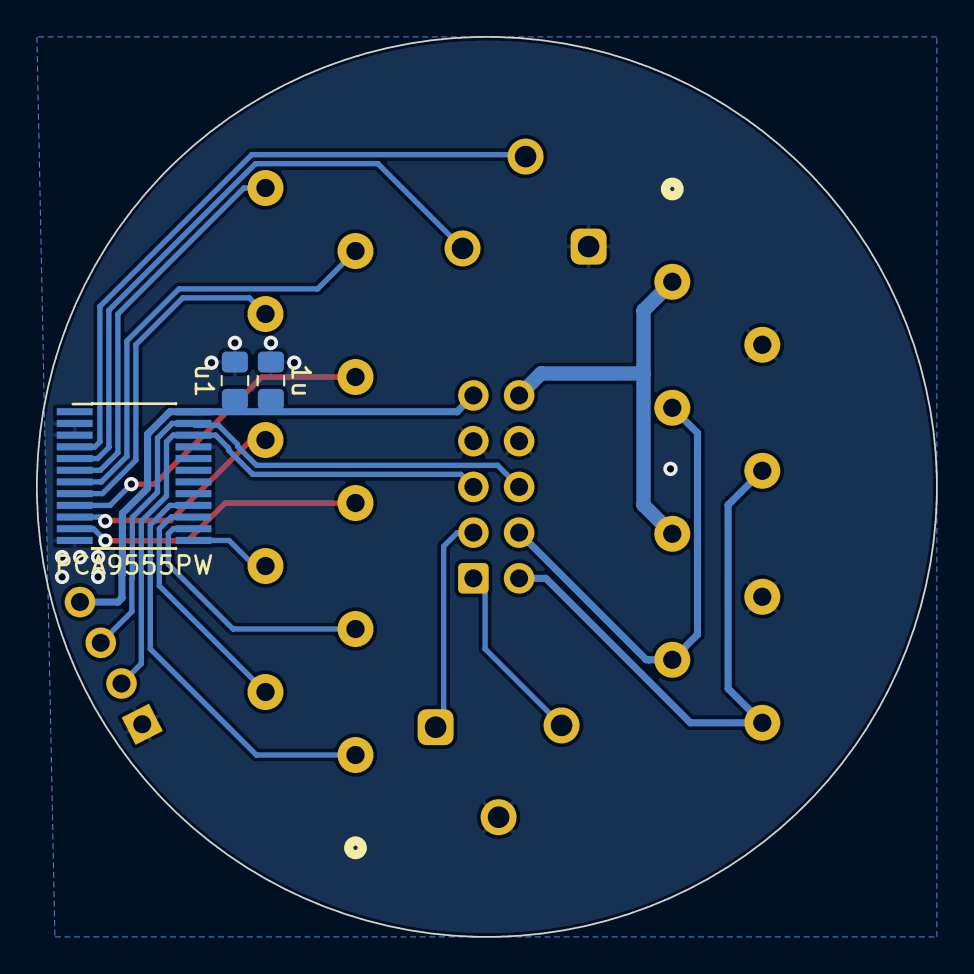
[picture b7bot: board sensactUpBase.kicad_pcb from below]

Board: 2 copper layers, 50.0 x 50.0 mm, 10 parts (3 on the bottom side), 21 nets.
